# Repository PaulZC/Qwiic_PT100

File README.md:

# Qwiic PT100

### We've moved!

This repo has a new home over at [SparkFun](https://github.com/sparkfun/Qwiic_PT100_ADS122C04)

_"So long, and thanks for all the fish."_
_(Douglas Adams)_

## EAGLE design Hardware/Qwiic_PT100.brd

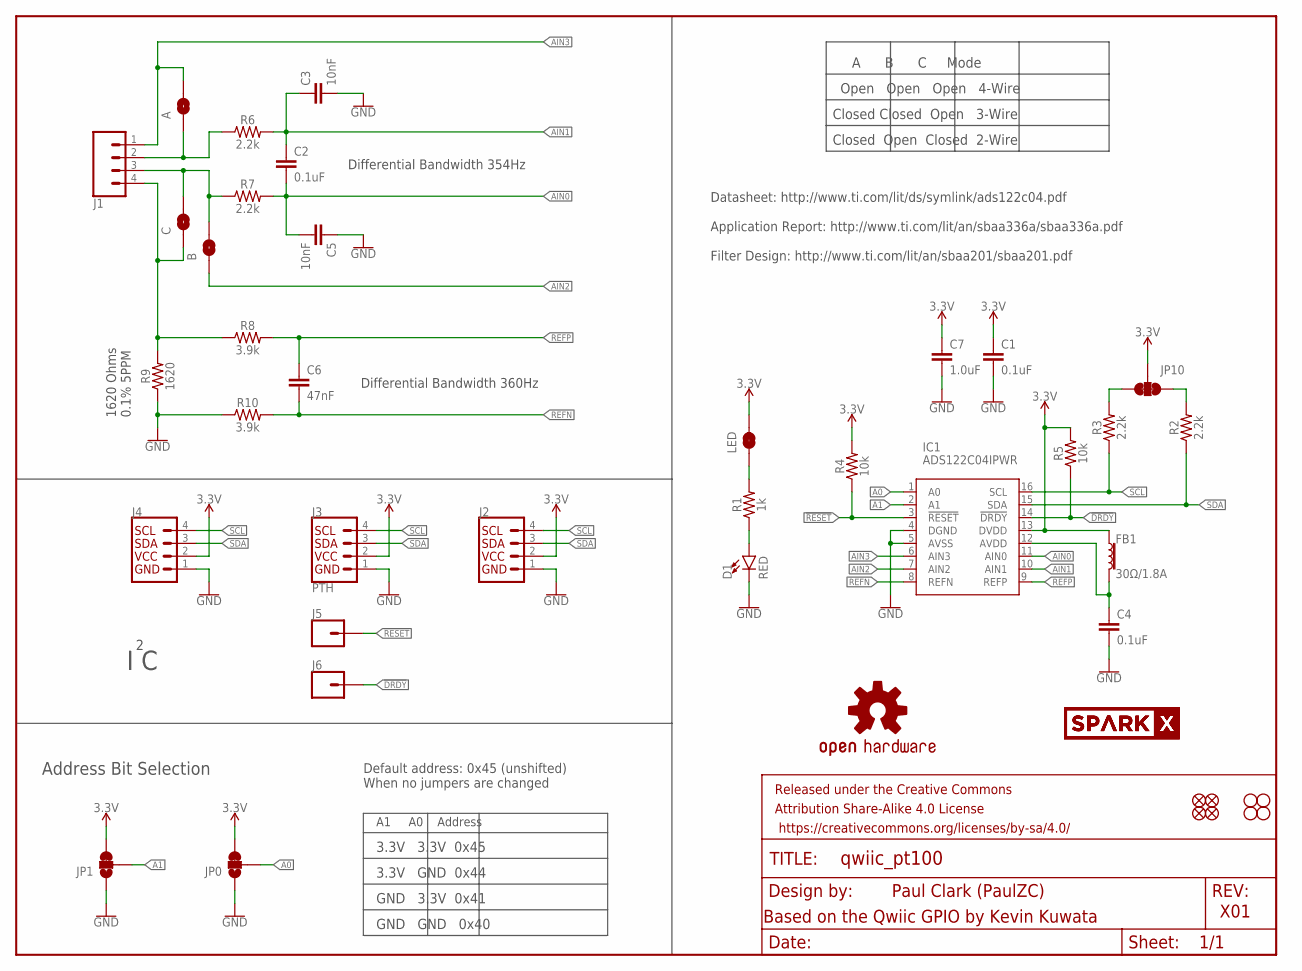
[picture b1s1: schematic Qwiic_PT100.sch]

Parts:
A: JUMPER-SMT_2_NO_SILK_ROUND; SMT-JUMPER_2_NO_SILK_ROUND
B: JUMPER-SMT_2_NO_SILK_ROUND; SMT-JUMPER_2_NO_SILK_ROUND
C: JUMPER-SMT_2_NO_SILK_ROUND; SMT-JUMPER_2_NO_SILK_ROUND
C1, C2, C4: 0.1uF; 0603
C3, C5: 10nF; 0603
C6: 47nF; 0603
C7: 1.0uF; 0603
D1: RED; LED-0603
FB1: 30Ω/1.8A; 0603
FD1, FD2: FIDUCIAL1X2; FIDUCIAL-1X2
FRAME1: FRAME-LETTER; CREATIVE_COMMONS
H1, H2: STAND-OFF
IC1: ADS122C04IPWR; SOP65P640X120-16N
J1: CONN_04LATCH; LATCHTERMINAL-5MM-4
J2, J4: QWIIC_RIGHT_ANGLE; JST04_1MM_RA
J3: PTH; 1X04_NO_SILK
J5, J6: CONN_01PTH_NO_SILK_YES_STOP; 1X01_NO_SILK
JP0, JP1: JUMPER-SMT_3_1-NC_TRACE_SILK; SMT-JUMPER_3_1-NC_TRACE_SILK
JP2, JP6: FIDUCIAL1X2; FIDUCIAL-1X2
JP3, JP4: STAND-OFF
JP10: JUMPER-SMT_3_2-NC_TRACE_SILK; SMT-JUMPER_3_2-NC_TRACE_SILK
LED: JUMPER-SMT_2_NC_TRACE_SILK; SMT-JUMPER_2_NC_TRACE_SILK
LOGO1: OSHW-LOGOMINI; OSHW-LOGO-MINI
R1: 1k; 0603
R2, R3, R6, R7: 2.2k; 0603
R4, R5: 10k; 0603
R8, R10: 3.9k; 0603
R9: 1620; 0603
U$1, U$2: SPARKX-LOGO3; SPARKX-SMALL

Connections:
3.3V: C1.1, C7.1, FB1.1, IC1.13 (DVDD), J2.2, J3.2, J4.2, JP0.3, JP1.3, JP10.2, LED.2, R4.2, R5.2
!DRDY: IC1.14 (!DRDY), J6.1, R5.1
!RESET: IC1.3 (!RESET), J5.1, R4.1
A0: IC1.1 (A0), JP0.2
A1: IC1.2 (A1), JP1.2
AIN0: C2.2, C5.2, IC1.11 (AIN0), R7.2
AIN1: C2.1, C3.1, IC1.10 (AIN1), R6.2
AIN2: B.1, IC1.7 (AIN2)
AIN3: A.2, IC1.6 (AIN3), J1.1
GND: C1.2, C3.2, C4.2, C5.1, C7.2, D1.C, IC1.4 (DGND), IC1.5 (AVSS), J2.1, J3.1, J4.1, JP0.1, JP1.1, R9.1, R10.1
unnamed: A.1, J1.2, R6.1
unnamed: D1.A, R1.1
unnamed: LED.1, R1.2
unnamed: C4.1, FB1.2, IC1.12 (AVDD)
unnamed: B.2, C.2, J1.3, R7.1
unnamed: C.1, J1.4, R8.1, R9.2
REFN: C6.2, IC1.8 (REFN), R10.2
REFP: C6.1, IC1.9 (REFP), R8.2
SCL: IC1.16 (SCL), J2.4, J3.4, J4.4, R3.1
SCL_PU1: JP10.1, R2.2
SDA: IC1.15 (SDA), J2.3, J3.3, J4.3, R2.1
SDA_PU1: JP10.3, R3.2

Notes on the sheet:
Paul Clark (PaulZC)
X01
I C
Address Bit Selection
A1 A0 Address
3.3V 3.3V 0x45
3.3V GND 0x44
GND 3.3V 0x41
GND GND 0x40
Default address: 0x45 (unshifted) When no jumpers are changed
Based on the Qwiic GPIO by Kevin Kuwata
A B C Mode
Open Open Open 4-Wire
Closed Closed Open 3-Wire
Closed Open Closed 2-Wire
Datasheet: http://www.ti.com/lit/ds/symlink/ads122c04.pdf Application Report: http://www.ti.com/lit/an/sbaa336a/sbaa336a.pdf Filter Design: http://www.ti.com/lit/an/sbaa201/sbaa201.pdf
1620 Ohms 0.1% 5PPM
Differential Bandwidth 354Hz
Differential Bandwidth 360Hz

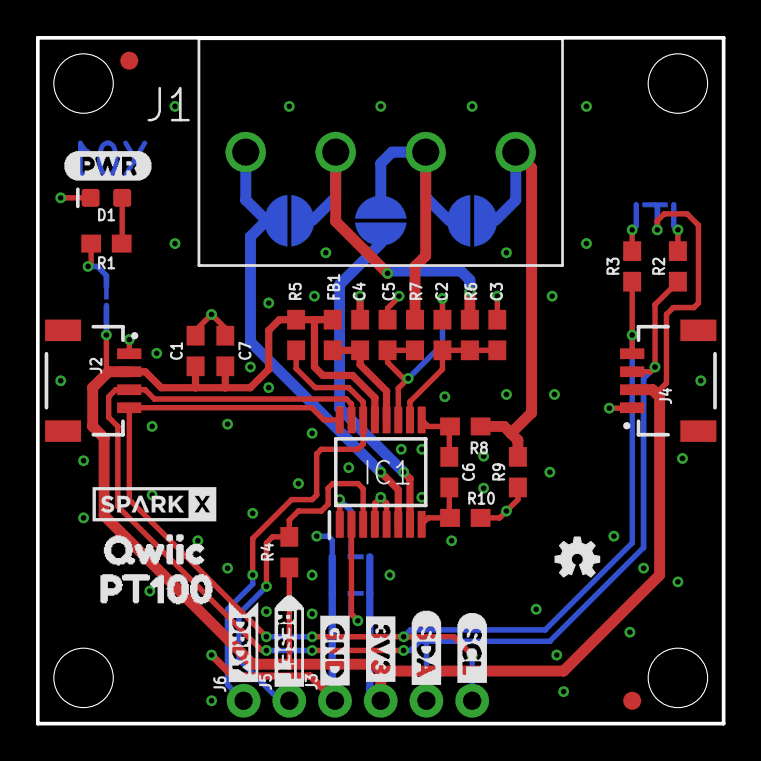
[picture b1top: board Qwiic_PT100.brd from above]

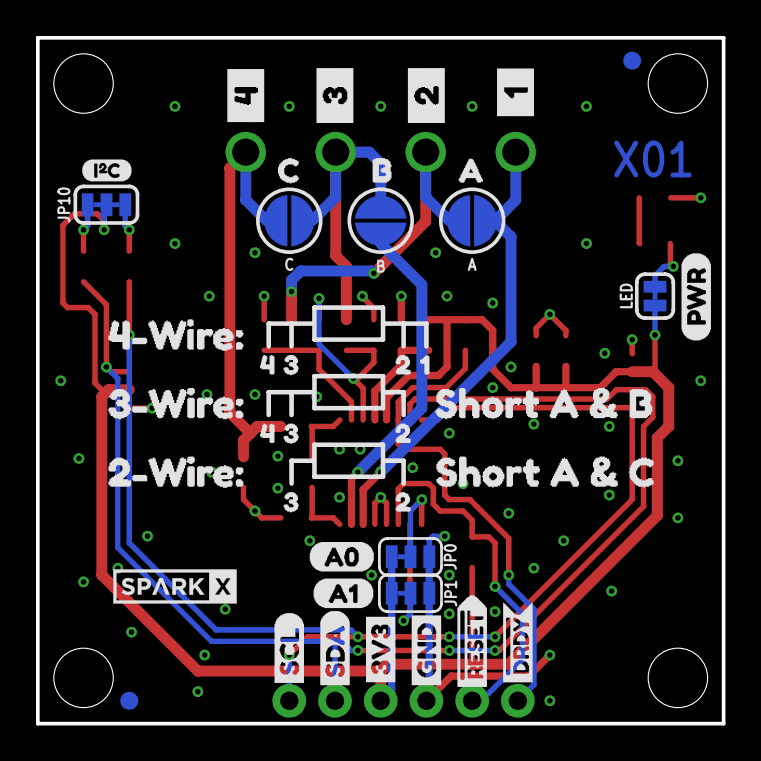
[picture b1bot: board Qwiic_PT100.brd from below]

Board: 2 copper layers, 38.1 x 38.1 mm, 85 parts (41 on the bottom side), 22 nets.

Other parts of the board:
U$3, U$26: 3V33
U$4: _1_0
U$5: A11
U$6: _2_0
U$7, U$25: GND4
U$8: PT1000
U$9: SCL6
U$10: SDA5
U$11: A00
U$12: _3_0
U$13: _4_0
U$14, U$15: #DRDY0
U$16, U$17: #RESET0
U$18: A0
U$19: B0
U$20: I_SUPER2_C-()-03
U$22: C0
U$23: SCL0
U$24: SDA1
U$29: 15
U$30, U$44: 40
U$31: 2#WIRE#0
U$32: QWIIC1
U$33, U$37, U$46: 20
U$34, U$38, U$47: 31
U$36: 3#WIRE#0
U$39, U$40: PWR0
U$41: 4#WIRE#0
U$42: SHORT_A_#_B0
U$43: SHORT_A_#_C0

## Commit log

2020-05-05 Tweaks
2020-05-06 Ready for manufacture
2020-05-06 Add panel files
2020-05-30 Added the link to the SparkFun repo

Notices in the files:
parts and their libraries:
SparkFun-Resistors: Licensing: Creative Commons ShareAlike 4.0 International - https://creativecommons.org/licenses/by-sa/4.0
SparkFun-Aesthetics: Released under the Creative Commons Attribution Share-Alike 4.0 License
SparkFun-Aesthetics: https://creativecommons.org/licenses/by-sa/4.0
